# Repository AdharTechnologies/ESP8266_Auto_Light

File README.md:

# ESP8266_Auto_Light

# Description
This is a ESP8266 D1 Mini and LDR based Automatic Light Switch using Blynk IoT Platform.
PCB files and code is given. Slight change in the code is needed and you are good to go.

kindly read this blog for full understanding: https://docs.google.com/document/d/e/2PACX-1vSuzVgyN2Nl00XQuRrzeUk8ifh-LkRNRmgxA4kx9S971_vfm6ms2yWArOn73SiwYcZxrXWrQjWCM0_2/pub

# Embedded CTG

Facebook:https://www.facebook.com/profile.php?id=61558436573900

Youtube: https://www.youtube.com/@EmbeddedCTG

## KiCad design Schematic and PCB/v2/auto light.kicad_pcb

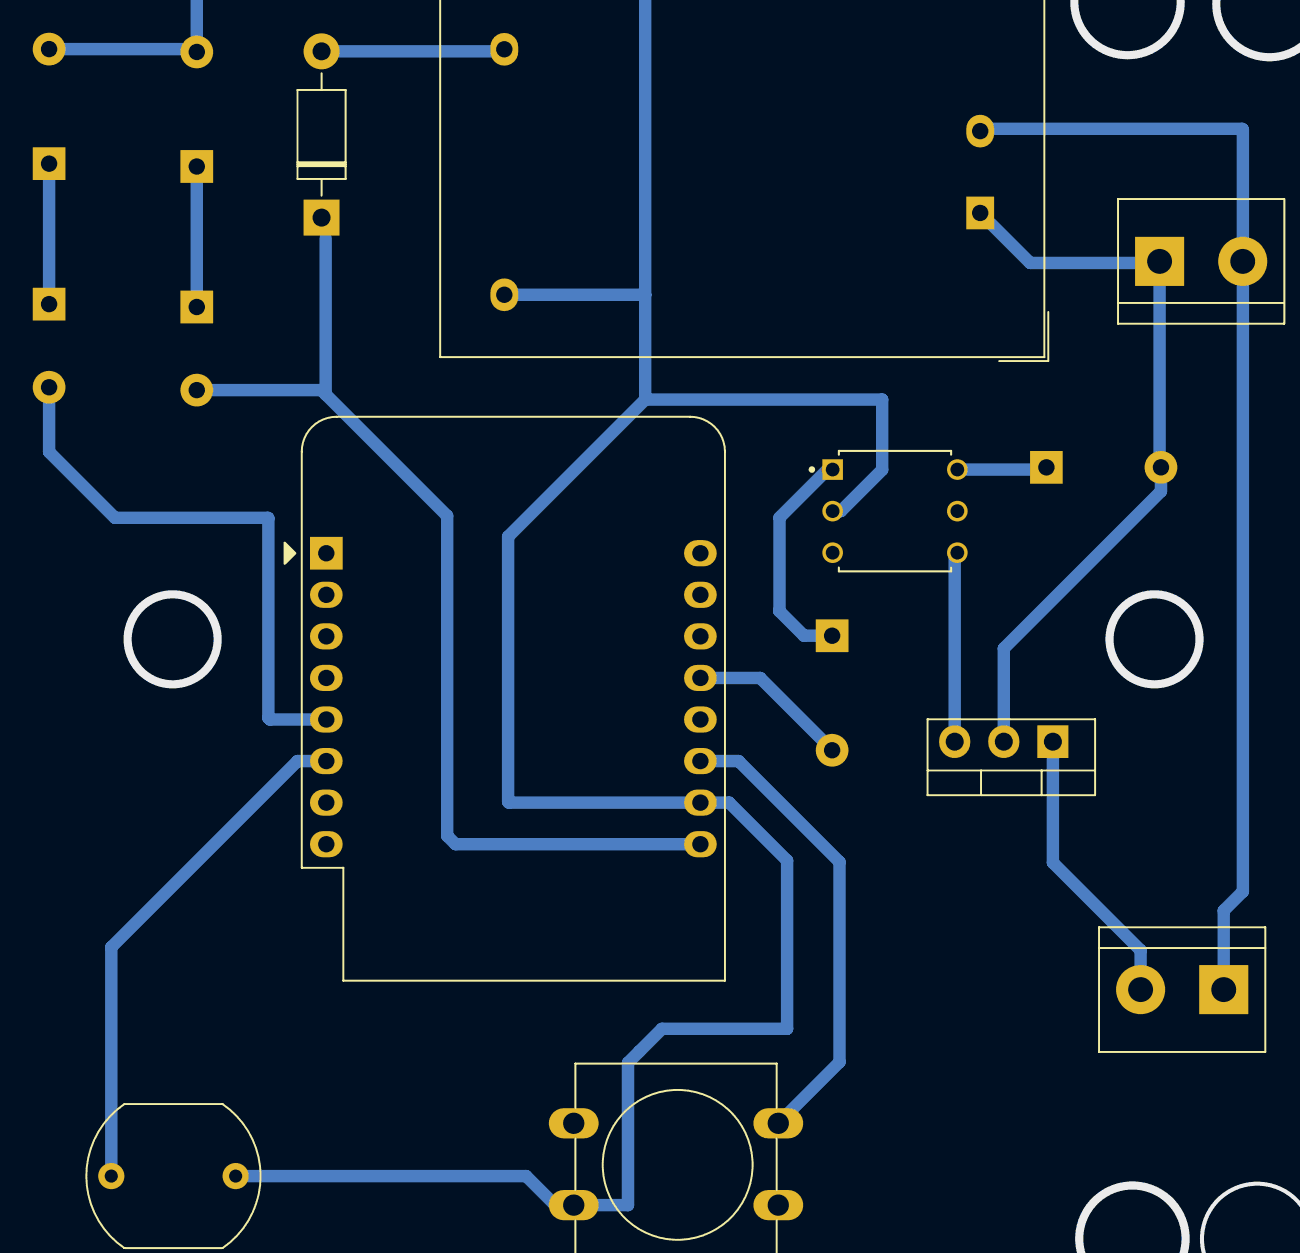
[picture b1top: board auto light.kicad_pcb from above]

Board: 2 copper layers, 5 parts (0 on the bottom side), 5 nets.

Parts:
D1: 1N4007; D_DO-41_SOD81_P10.16mm_Horizontal
PS1: HLK-PM01; Converter_ACDC_Hi-Link_HLK-PMxx
Q1: BT136-500; TO-220-3_Vertical
R1: LDR03; R_LDR_10x8.5mm_P7.6mm_Vertical
U1: WeMos_D1_mini; WEMOS_D1_mini_light

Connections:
unnamed: D1.2 (A), PS1.4 (+Vout)
unnamed: D1.1 (K), U1.9 (5V)
unnamed: PS1.3 (-Vout), R1.1, U1.10 (GND)
unnamed: PS1.1 (AC/L), Q1.2 (A2)
unnamed: R1.2, U1.6 (MOSI/D7)

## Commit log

2024-09-26 README.md
